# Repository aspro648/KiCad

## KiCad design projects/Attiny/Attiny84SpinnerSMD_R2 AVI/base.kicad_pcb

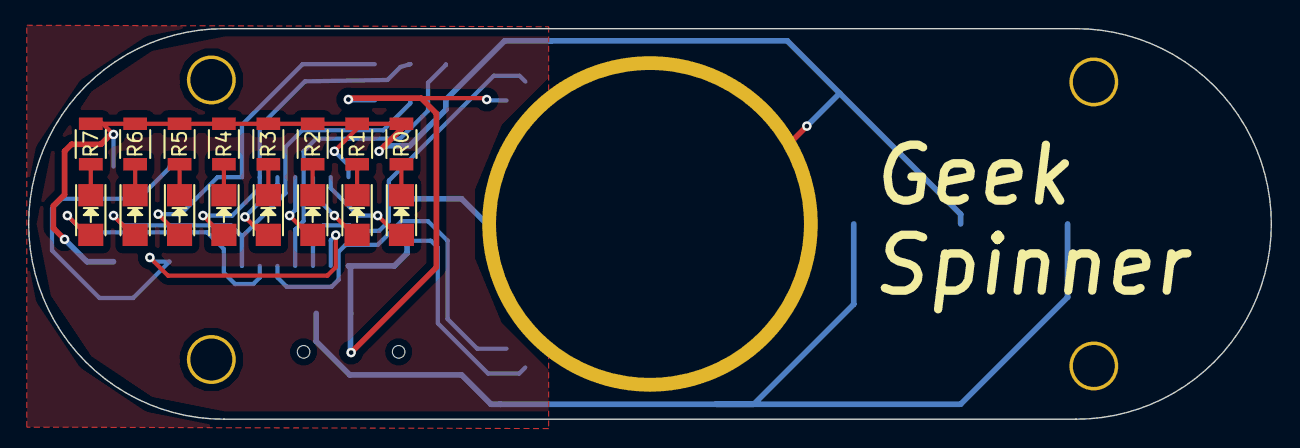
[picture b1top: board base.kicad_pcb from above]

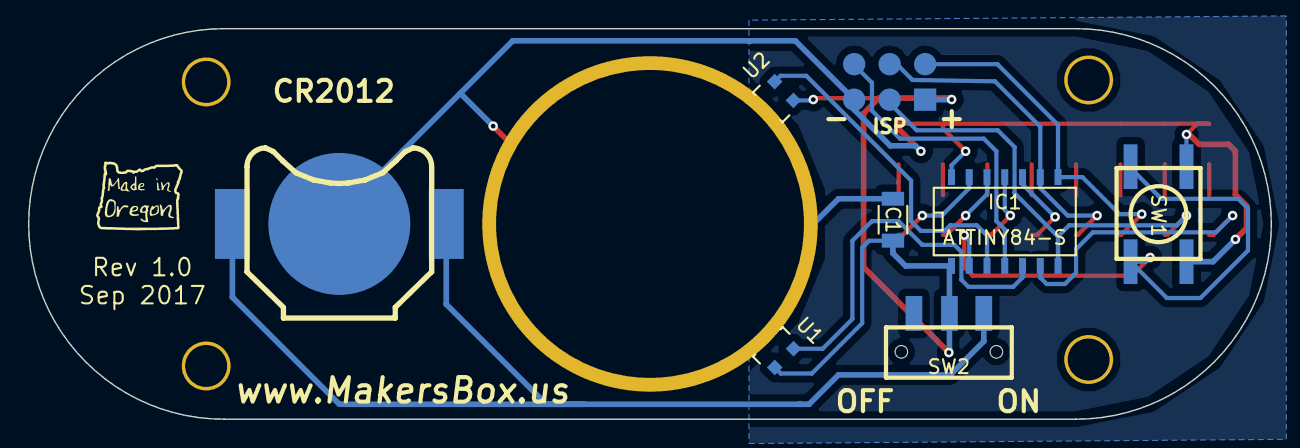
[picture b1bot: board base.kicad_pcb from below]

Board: 2 copper layers, 88.9 x 27.9 mm, 30 parts (8 on the bottom side), 23 nets.

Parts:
BT1: Battery; BATT_12mm
C1: 0.1 uF; C_1206
CON1: AVR-ISP-6
D0, D1, D2, D3, D4, D5, D6, D7: LED; LED-1206
IC1: ATTINY84-S; SOIC-14_N
P1: CONN_01X01; Pin_Header_Straight_1x01
P2, P2#2, P2#3, P2#4: CONN_01X01; Lego_Drill
R0, R1, R2, R3, R4, R5, R6, R7: 330; R_1206
SW1: SW_PUSH; SW_SMD_PUSH
SW2: SPST; SPST_SMD
U1, U2: MLX92231; SOT-23
VAL: MadeInOregonRev25

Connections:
+BATT: C1.1, CON1.2, IC1.1, SW2.2, U1.1, U2.1
GND: BT1.2, C1.2, CON1.6, IC1.14, P1.1, R0.2, R1.2, R2.2, R3.2, R4.2, R5.2, R6.2, R7.2, SW1.2, U1.2, U2.2
unnamed: BT1.1, SW2.1
unnamed: CON1.1, D5.2, IC1.8
unnamed: CON1.3, D4.2, IC1.9
unnamed: CON1.4, D6.2, IC1.7
unnamed: CON1.5, IC1.4
unnamed: D0.1, R0.1
unnamed: D0.2, IC1.13
unnamed: D1.1, R1.1
unnamed: D1.2, IC1.12
unnamed: D2.1, R2.1
unnamed: D2.2, IC1.11
unnamed: D3.1, R3.1
unnamed: D3.2, IC1.10
unnamed: D4.1, R4.1
unnamed: D5.1, R5.1
unnamed: D6.1, R6.1
unnamed: D7.1, R7.1
unnamed: D7.2, IC1.6
unnamed: IC1.2, SW1.1
unnamed: IC1.3, U2.3
unnamed: IC1.5, U1.3

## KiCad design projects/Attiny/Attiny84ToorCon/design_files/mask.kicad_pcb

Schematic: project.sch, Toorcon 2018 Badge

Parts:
BT1: Battery; BATT_CR2032_SMD
C1: 0.1 uF; C_1206
CON1: AVR-ISP-6
D1, D2: LED; LED-1206
D3, D4: LED; LED-0805
D5, D6: LED; LED-0603
D7: LED; LED_0402
D8: LED; LED_0201
P0, P1: CONN_01X01; Pin_Header_Straight_1x01
P2, P3, P4, P5, P6, P7, P8, P9: CONN_01X01; testPad
PG1, PG2, PG3, PG4, PG5, PG6, PG7, PG8: CONN_01X01; testPad
R1, R2: 100; R_1206
R3, R4: 100; R_0805
R5, R6: 100; R_0603
R7: 100; R_0402
R8: 100; R_0201
SW1: SW_SPDT; SPST_SMD
SW2: Fingerprint; R_0201
U1: ATTINY84A-SSU; SOIC-14_3.9x8.7mm_Pitch1.27mm
X1: Badgelife_shitty_connector; Badgelife-Shitty-2x2

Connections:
+BATT: C1.1, CON1.2, SW1.3 (B), U1.1 (VCC), X1.1
/MISO: CON1.1, D2.2 (A), P3.1, U1.8 ((PCINT5/DO/MISO/OC1B/ADC5)PA5)
/MOSI: CON1.4, D3.2 (A), P4.1, U1.7 ((PCINT6/SDA/DI/MOSI/OC1A/ADC6)PA6), X1.4
/RESET: CON1.5, U1.4 ((PCINT11/dW/~RESET~)PB3)
/SCK: CON1.3, P2.1, R1.1, U1.9 ((PCINT4/USCK/SCL/T1/ADC4)PA4), X1.3
GND: BT1.2, C1.2, CON1.6, SW2.2, U1.14 (GND), X1.2
unnamed: BT1.1, SW1.1 (C)
unnamed: D1.1 (K), D4.1 (K), PG1.1, PG2.1, PG3.1, PG4.1, PG5.1, PG6.1, PG7.1, PG8.1, R2.2, R3.2, R5.2, R6.2, R7.2, R8.2, U1.2 ((PCINT8/CLKI/XTAL1)PB0), U1.3 ((PCINT9/XTAL2)PB1)
unnamed: D1.2 (A), R1.2
unnamed: D2.1 (K), R2.1
unnamed: D3.1 (K), R3.1
unnamed: D4.2 (A), R4.2
unnamed: D5.1 (K), R5.1
unnamed: D5.2 (A), P6.1, U1.11 ((PCINT2/AIN1/ADC2)PA2)
unnamed: D6.1 (K), R6.1
unnamed: D6.2 (A), P7.1, U1.12 ((PCINT1/AIN0/ADC1)PA1)
unnamed: D7.1 (K), R7.1
unnamed: D7.2 (A), P8.1, U1.13 ((PCINT0/AREF/ADC0)PA0)
unnamed: D8.1 (K), R8.1
unnamed: D8.2 (A), P9.1, U1.10 ((PCINT3/T0/ADC3)PA3)
unnamed: P5.1, R4.1, U1.5 ((PCINT10/CKOUT/OC0A/INT0)PB2)
unnamed: SW2.1, U1.6 ((PCINT7/ICP/OC0B/ADC7)PA7)

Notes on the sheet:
D10
D3/A7
https://hackaday.io/project/52950-defcon-26-shitty-add-ons

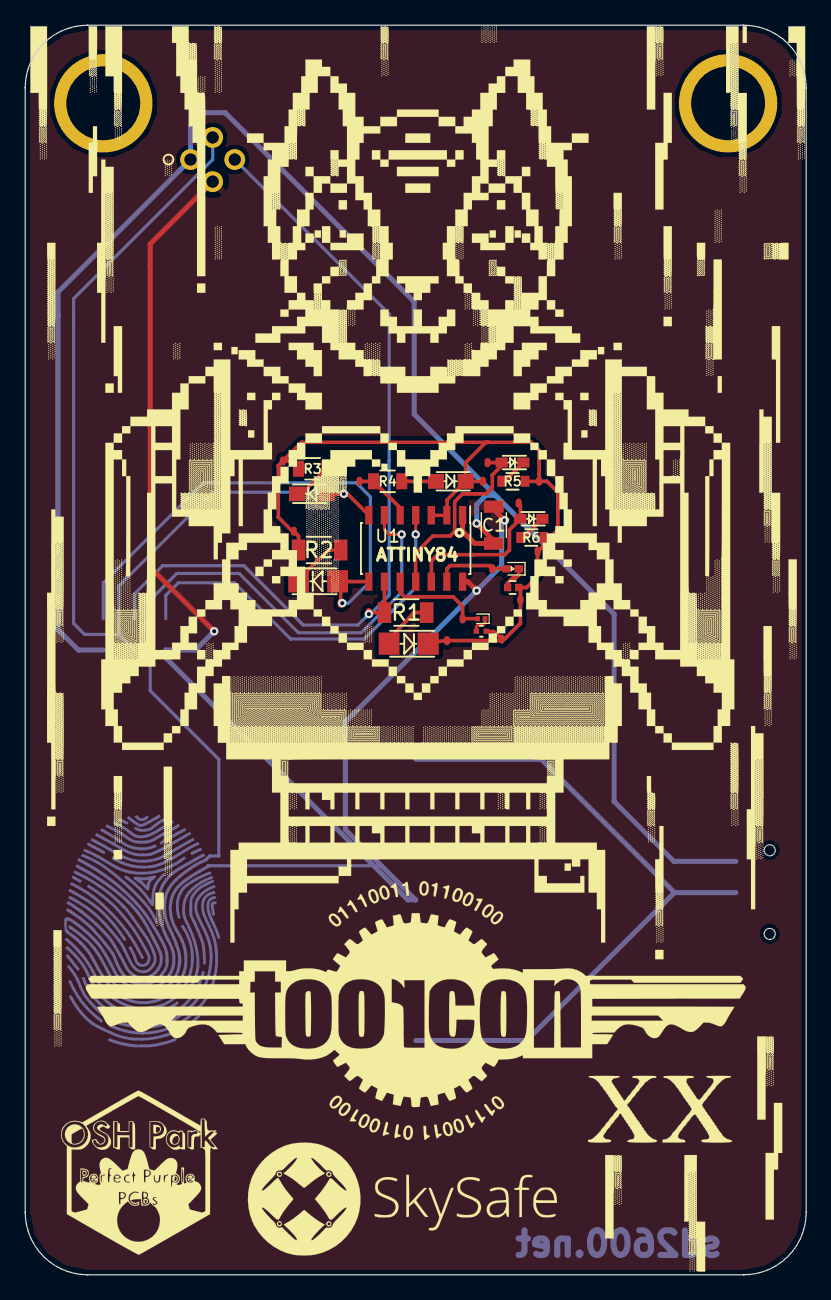
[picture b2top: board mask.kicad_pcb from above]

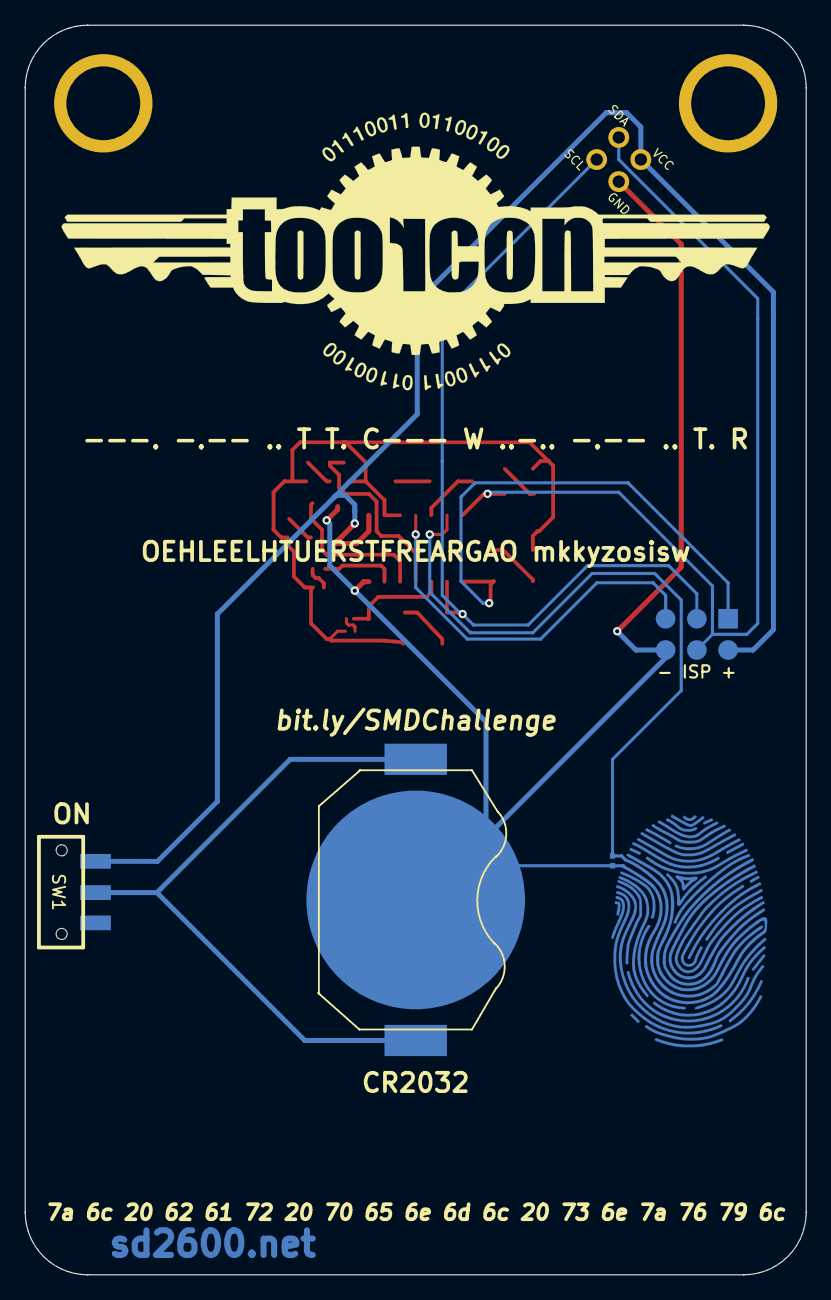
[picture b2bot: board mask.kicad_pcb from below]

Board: 2 copper layers, 63.5 x 101.6 mm, 41 parts (4 on the bottom side), 22 nets.
